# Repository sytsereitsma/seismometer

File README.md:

MC3479
NSCDJJN005NDUNV

# Filters
https://www.allaboutcircuits.com/video-tutorials/op-amps-low-pass-and-high-pass-active-filters/
http://sim.okawa-denshi.jp/en/OPstool.php
https://tools.analog.com/en/filterwizard/

https://electronics.stackexchange.com/questions/55233/how-do-you-simulate-voltage-noise-with-ltspice
https://electronics.stackexchange.com/questions/291721/how-to-implement-frequency-sweep-in-transient-mode-in-ltspice

## LTSpice

`.step param freq list 0.01 0.1 1 2 4 8 10 12` en dan BV voltage source (misc components) met `V=0.015*sin(2*pi*freq*time)`

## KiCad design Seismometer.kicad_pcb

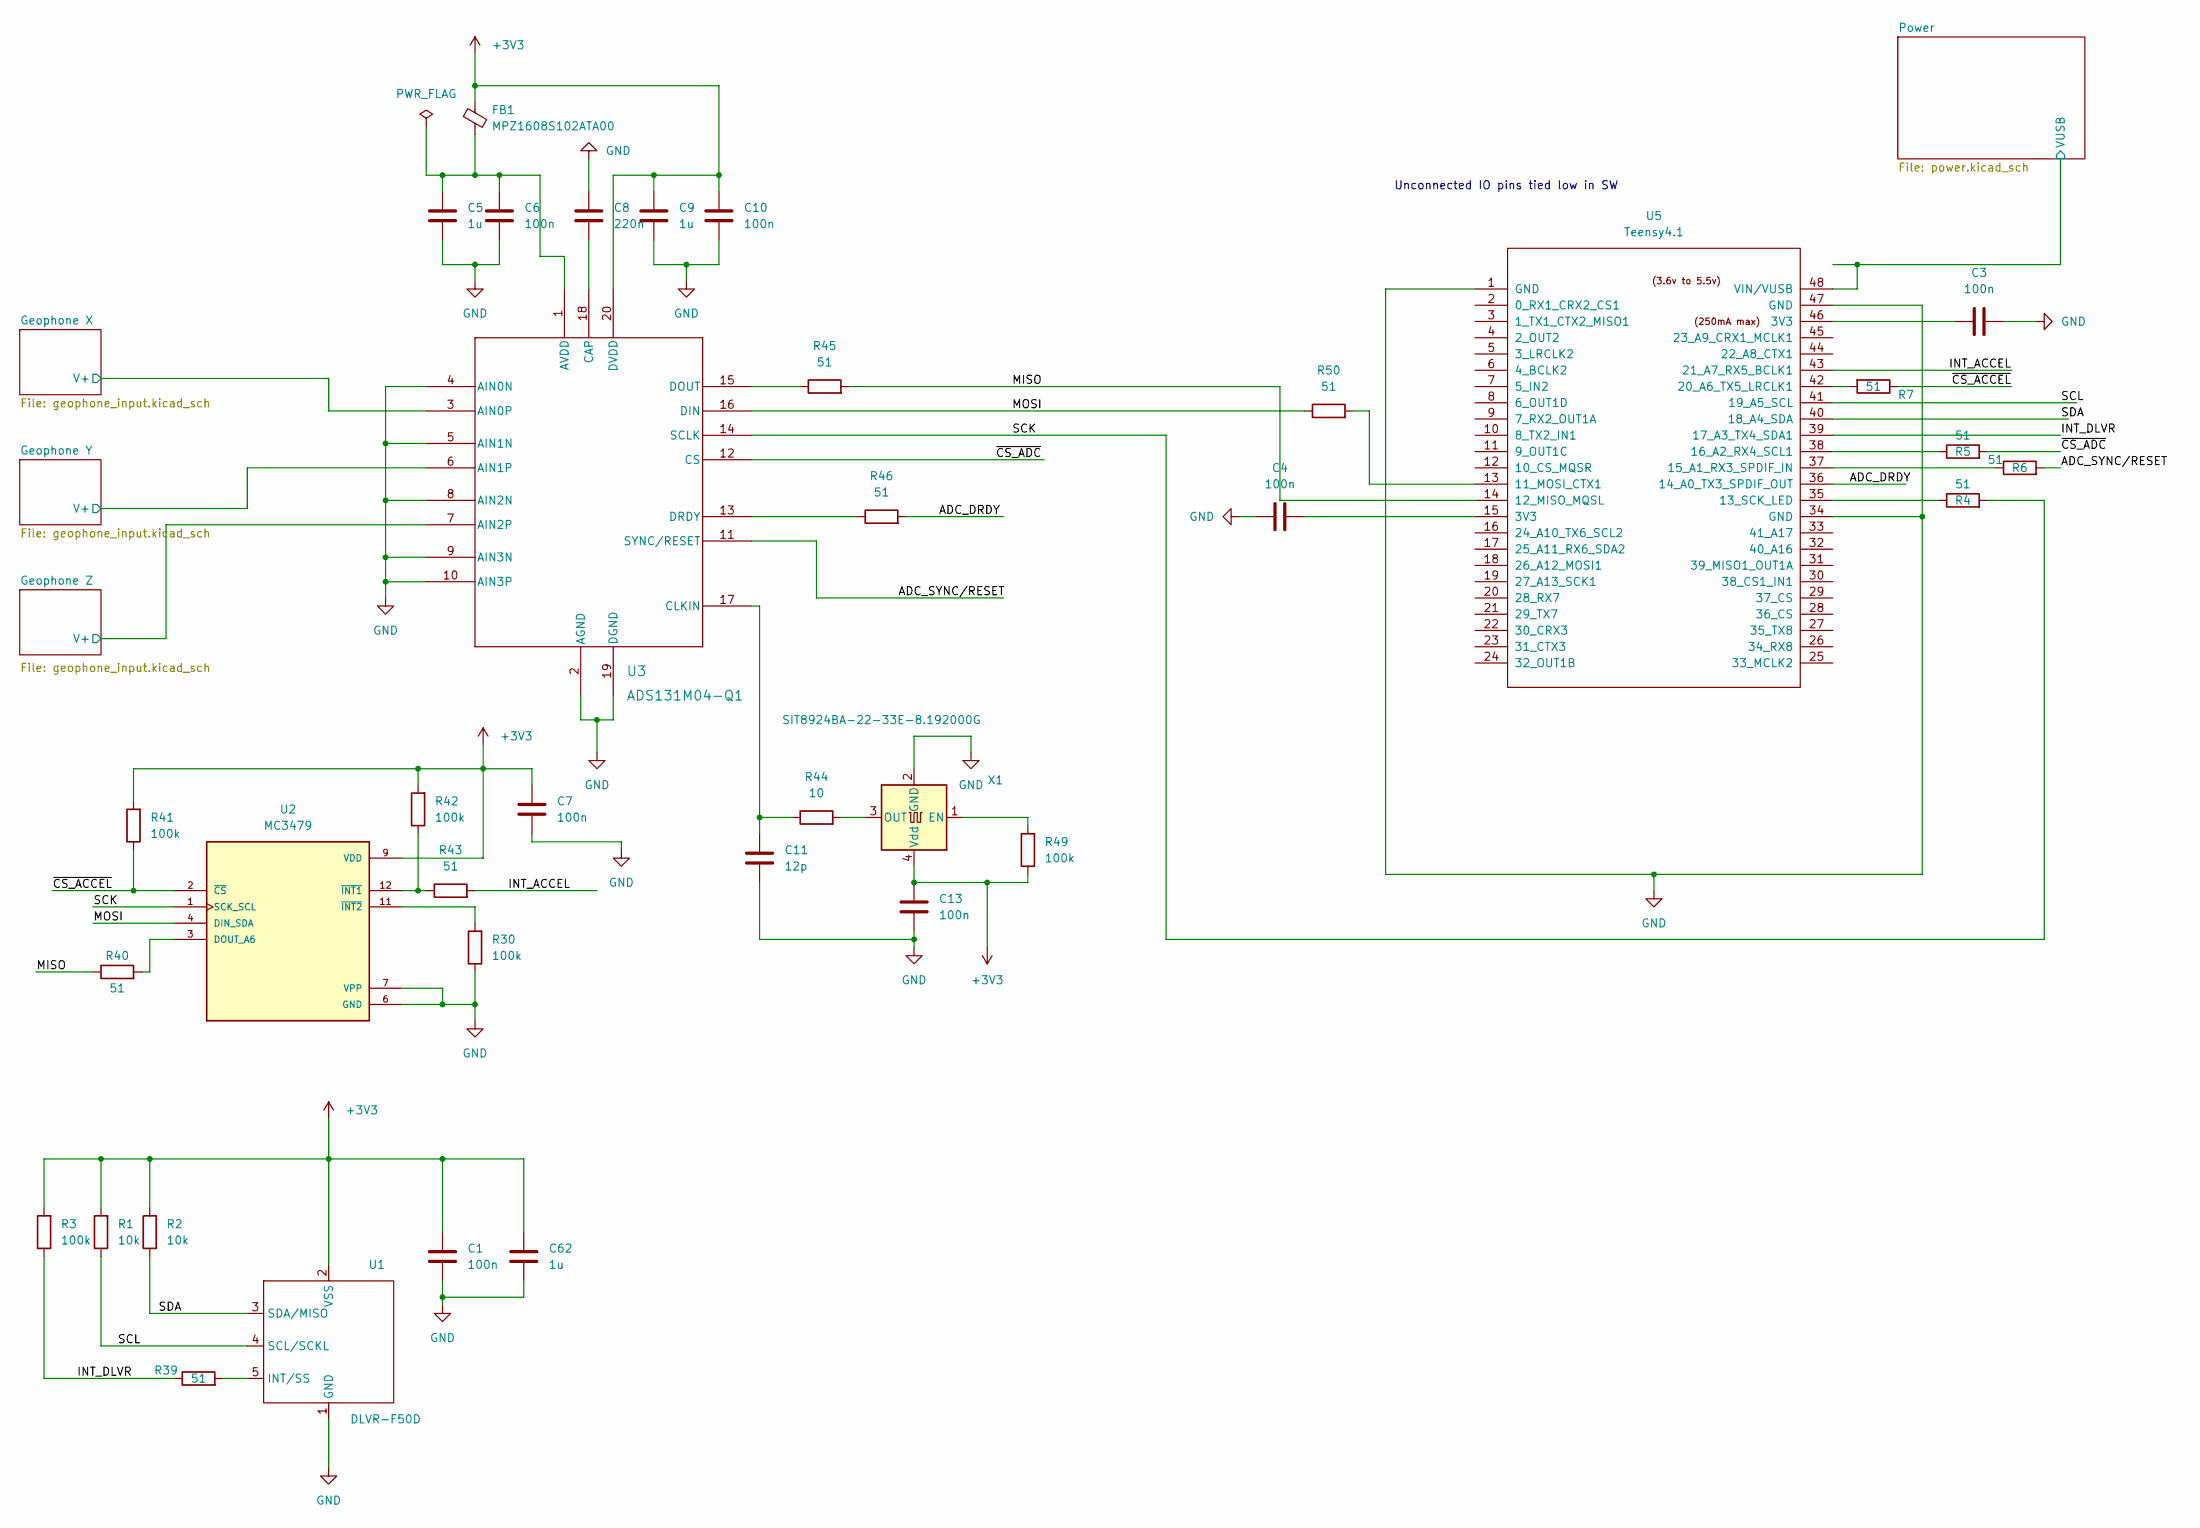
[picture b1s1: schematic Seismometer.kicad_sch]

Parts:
C1, C3, C4, C6, C7, C10, C13: 100n; C_0603_1608Metric_Pad1.08x0.95mm_HandSolder
C5, C9, C62: 1u; C_1206_3216Metric
C8: 220n; C_0603_1608Metric_Pad1.08x0.95mm_HandSolder
C11: 12p; C_0603_1608Metric_Pad1.08x0.95mm_HandSolder
FB1: MPZ1608S102ATA00; L_0805_2012Metric
R1, R2: 10k; R_0603_1608Metric
R3, R30, R41, R42, R49: 100k; R_0603_1608Metric
R4, R5, R6, R7, R39, R40, R43, R45, R46, R50: 51; R_0603_1608Metric
R44: 10; R_0603_1608Metric
U1: DLVR-F50D; DIP-8_W8.89mm_SMDSocket_LongPads
U2: MC3479; PQFN50P200X200X100-12N; PARTREV 1.1
U3: ADS131M04-Q1; TSSOP20_PW_TEX
U5: Teensy4.1; Teensy41_minimal
X1: SIT8924BA-22-33E-8.192000G; Oscillator_SMD_Abracon_ASE-4Pin_3.2x2.5mm

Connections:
+3V3: C1.1, C7.1, C9.1, C10.1, C13.1, C62.1, FB1.1, R1.2, R2.2, R3.2, R41.2, R42.2, R49.1, U1.2 (VSS), U2.9 (VDD), U3.20 (DVDD), X1.4 (Vdd); also elsewhere on the board
/ADC_DRDY: R46.2, U5.36 (14_A0_TX3_SPDIF_OUT)
/ADC_SYNC/RESET: R6.2, U3.11 (SYNC/RESET)
/Geophone X/V+: U3.3 (AIN0P); also elsewhere on the board
/Geophone Y/V+: U3.6 (AIN1P); also elsewhere on the board
/Geophone Z/V+: U3.7 (AIN2P); also elsewhere on the board
/INT_ACCEL: R43.2, U5.43 (21_A7_RX5_BCLK1)
/INT_DLVR: R3.1, R39.1, U5.39 (17_A3_TX4_SDA1)
/MISO: R40.1, R45.2, U5.14 (12_MISO_MQSL)
/MOSI: R50.1, U2.4 (DIN_SDA), U3.16 (DIN)
/Power/VUSB: U5.48 (VIN/VUSB); also elsewhere on the board
/SCK: R4.2, U2.1 (SCK_SCL), U3.14 (SCLK)
/SCL: R1.1, U1.4 (SCL/SCKL), U5.41 (19_A5_SCL)
/SDA: R2.1, U1.3 (SDA/MISO), U5.40 (18_A4_SDA)
/~CS_ACCEL: R7.1, R41.1, U2.2 (~CS)
/~CS_ADC: R5.2, U3.12 (CS)
GND: C1.2, C3.2, C4.1, C5.2, C6.2, C7.2, C8.1, C9.2, C10.2, C11.2, C13.2, C62.2, R30.1, U1.1 (GND), U2.6 (GND), U2.7 (VPP), U3.2 (AGND), U3.4 (AIN0N), U3.5 (AIN1N), U3.8 (AIN2N), U3.9 (AIN3N), U3.10 (AIN3P), U3.19 (DGND), U5.1 (GND), U5.34 (GND), U5.47 (GND), X1.2 (GND); also elsewhere on the board
unnamed: C3.1, U5.46 (3V3)
unnamed: C4.2, U5.15 (3V3)
unnamed: R39.2, U1.5 (INT/SS)
unnamed: R40.2, U2.3 (DOUT_A6)
unnamed: R42.1, R43.1, U2.12 (~INT1)
unnamed: R30.2, U2.11 (~INT2)
unnamed: C5.1, C6.1, FB1.2, U3.1 (AVDD)
unnamed: C8.2, U3.18 (CAP)
unnamed: C11.1, R44.1, U3.17 (CLKIN)
unnamed: R45.1, U3.15 (DOUT)
unnamed: R46.1, U3.13 (DRDY)
unnamed: R50.2, U5.13 (11_MOSI_CTX1)
unnamed: R4.1, U5.35 (13_SCK_LED)
unnamed: R6.1, U5.37 (15_A1_RX3_SPDIF_IN)
unnamed: R5.1, U5.38 (16_A2_RX4_SCL1)
unnamed: R7.2, U5.42 (20_A6_TX5_LRCLK1)
unnamed: R49.2, X1.1 (EN)
unnamed: R44.2, X1.3 (OUT)

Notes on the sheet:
Unconnected IO pins tied low in SW

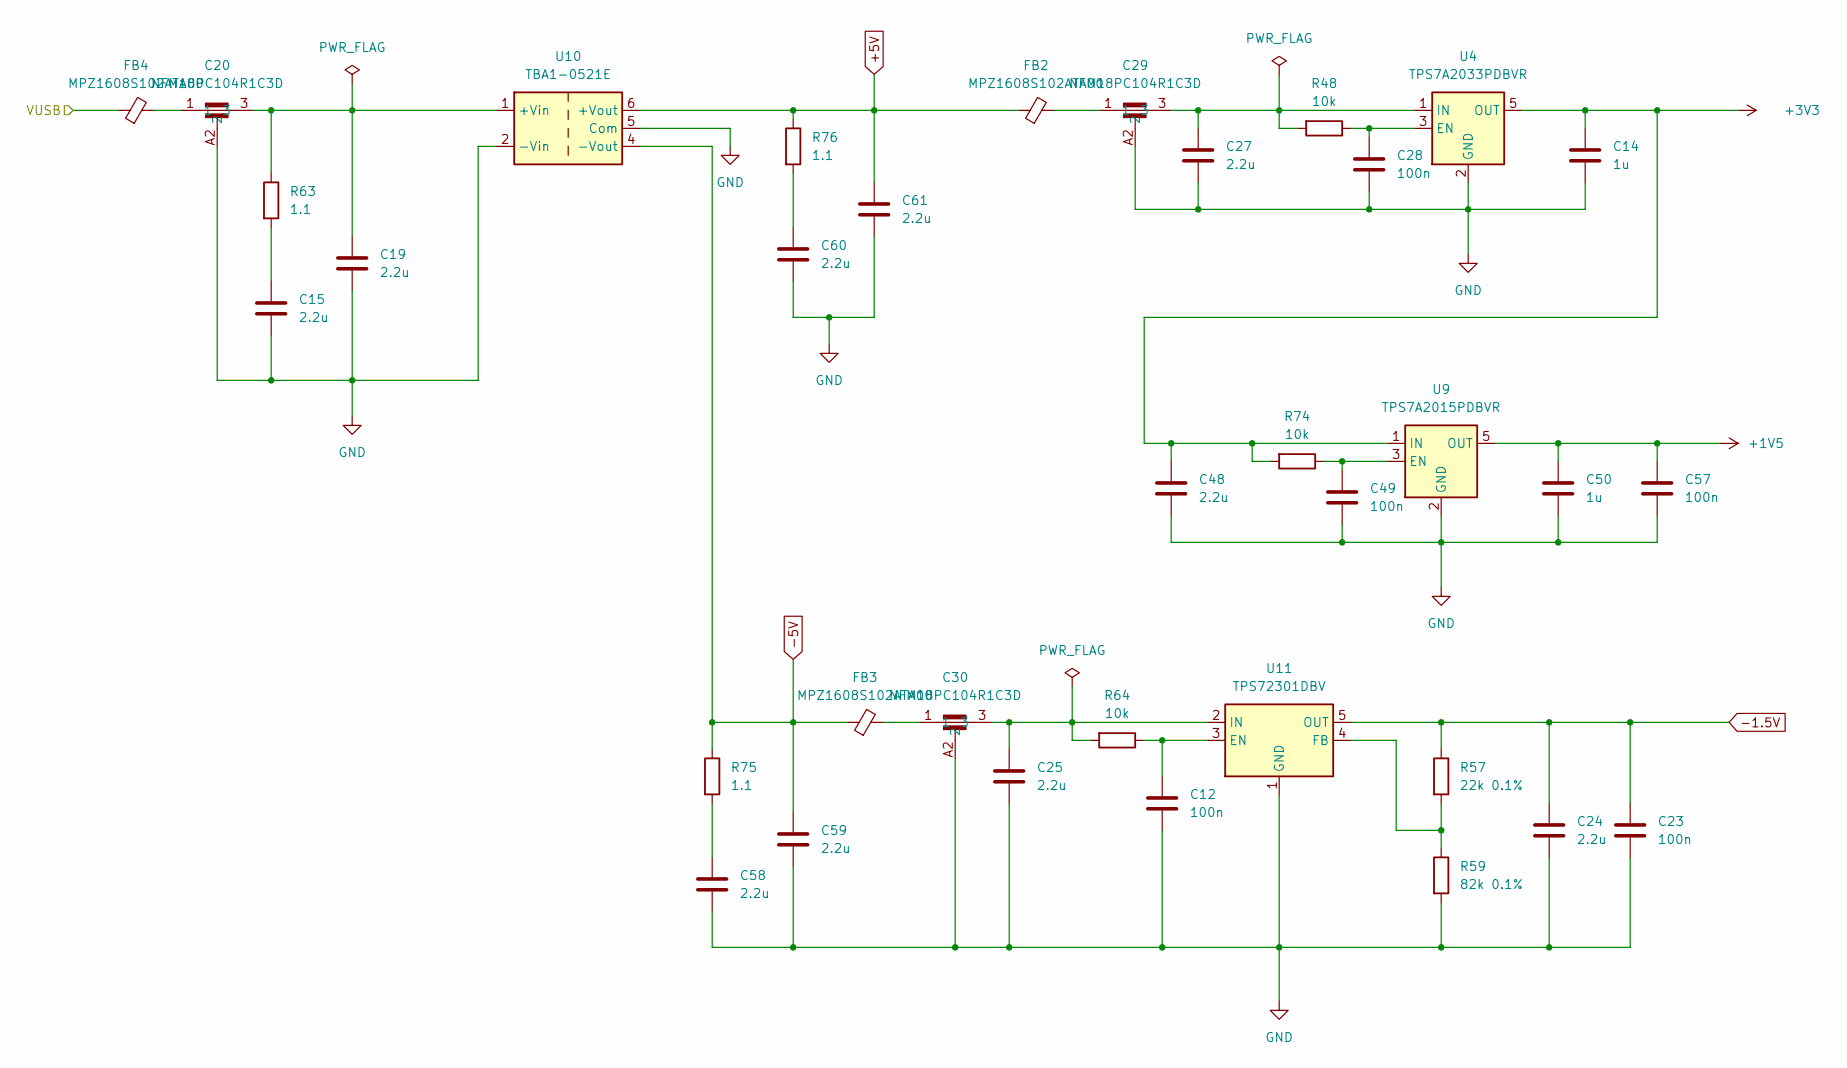
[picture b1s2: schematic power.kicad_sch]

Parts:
C12, C28, C49: 100n; C_0603_1608Metric_Pad1.08x0.95mm_HandSolder
C14, C50: 1u; C_1206_3216Metric
C15, C19, C24, C25, C27, C48, C58, C59, C60, C61: 2.2u; C_1206_3216Metric
C20, C29, C30: NFM18PC104R1C3D
C23, C57: 100n; C_0805_2012Metric
FB2, FB3, FB4: MPZ1608S102ATA00; L_0805_2012Metric
R48, R64, R74: 10k; R_0603_1608Metric
R57: 22k 0.1%; R_0603_1608Metric
R59: 82k 0.1%; R_0603_1608Metric
R63, R75, R76: 1.1; R_0603_1608Metric
U4: TPS7A2033PDBVR; SOT-23-5
U9: TPS7A2015PDBVR; SOT-23-5
U10: TBA1-0521E; Converter_DCDC_TRACO_TBA1-xxxxE_Dual_THT
U11: TPS72301DBV; SOT-23-5

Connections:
+1V5: C50.1, C57.1, U9.5 (OUT); also elsewhere on the board
+3V3: C14.1, C48.1, R74.2, U4.5 (OUT), U9.1 (IN); also elsewhere on the board
+5V: C61.1, FB2.1, R76.1, U10.6 (+Vout)
-1.5V: C23.1, C24.1, R57.1, U11.5 (OUT); also elsewhere on the board
-5V: C59.1, FB3.1, R75.1, U10.4 (-Vout)
/Power/VUSB: FB4.1; also elsewhere on the board
GND: C12.2, C14.2, C15.2, C19.2, C20.A2 (2), C20.B2 (4), C23.2, C24.2, C25.2, C27.2, C28.2, C29.A2 (2), C29.B2 (4), C30.A2 (2), C30.B2 (4), C48.2, C49.2, C50.2, C57.2, C58.2, C59.2, C60.2, C61.2, R59.2, U4.2 (GND), U9.2 (GND), U10.2 (-Vin), U10.5 (Com), U11.1 (GND); also elsewhere on the board
unnamed: C15.1, R63.2
unnamed: C20.1, FB4.2
unnamed: C29.1, FB2.2
unnamed: C30.1, FB3.2
unnamed: C58.1, R75.2
unnamed: C60.1, R76.2
unnamed: C28.1, R48.1, U4.3 (EN)
unnamed: C27.1, C29.3, R48.2, U4.1 (IN)
unnamed: C49.1, R74.1, U9.3 (EN)
unnamed: C19.1, C20.3, R63.1, U10.1 (+Vin)
unnamed: C12.1, R64.1, U11.3 (EN)
unnamed: R57.2, R59.1, U11.4 (FB)
unnamed: C25.1, C30.3, R64.2, U11.2 (IN)

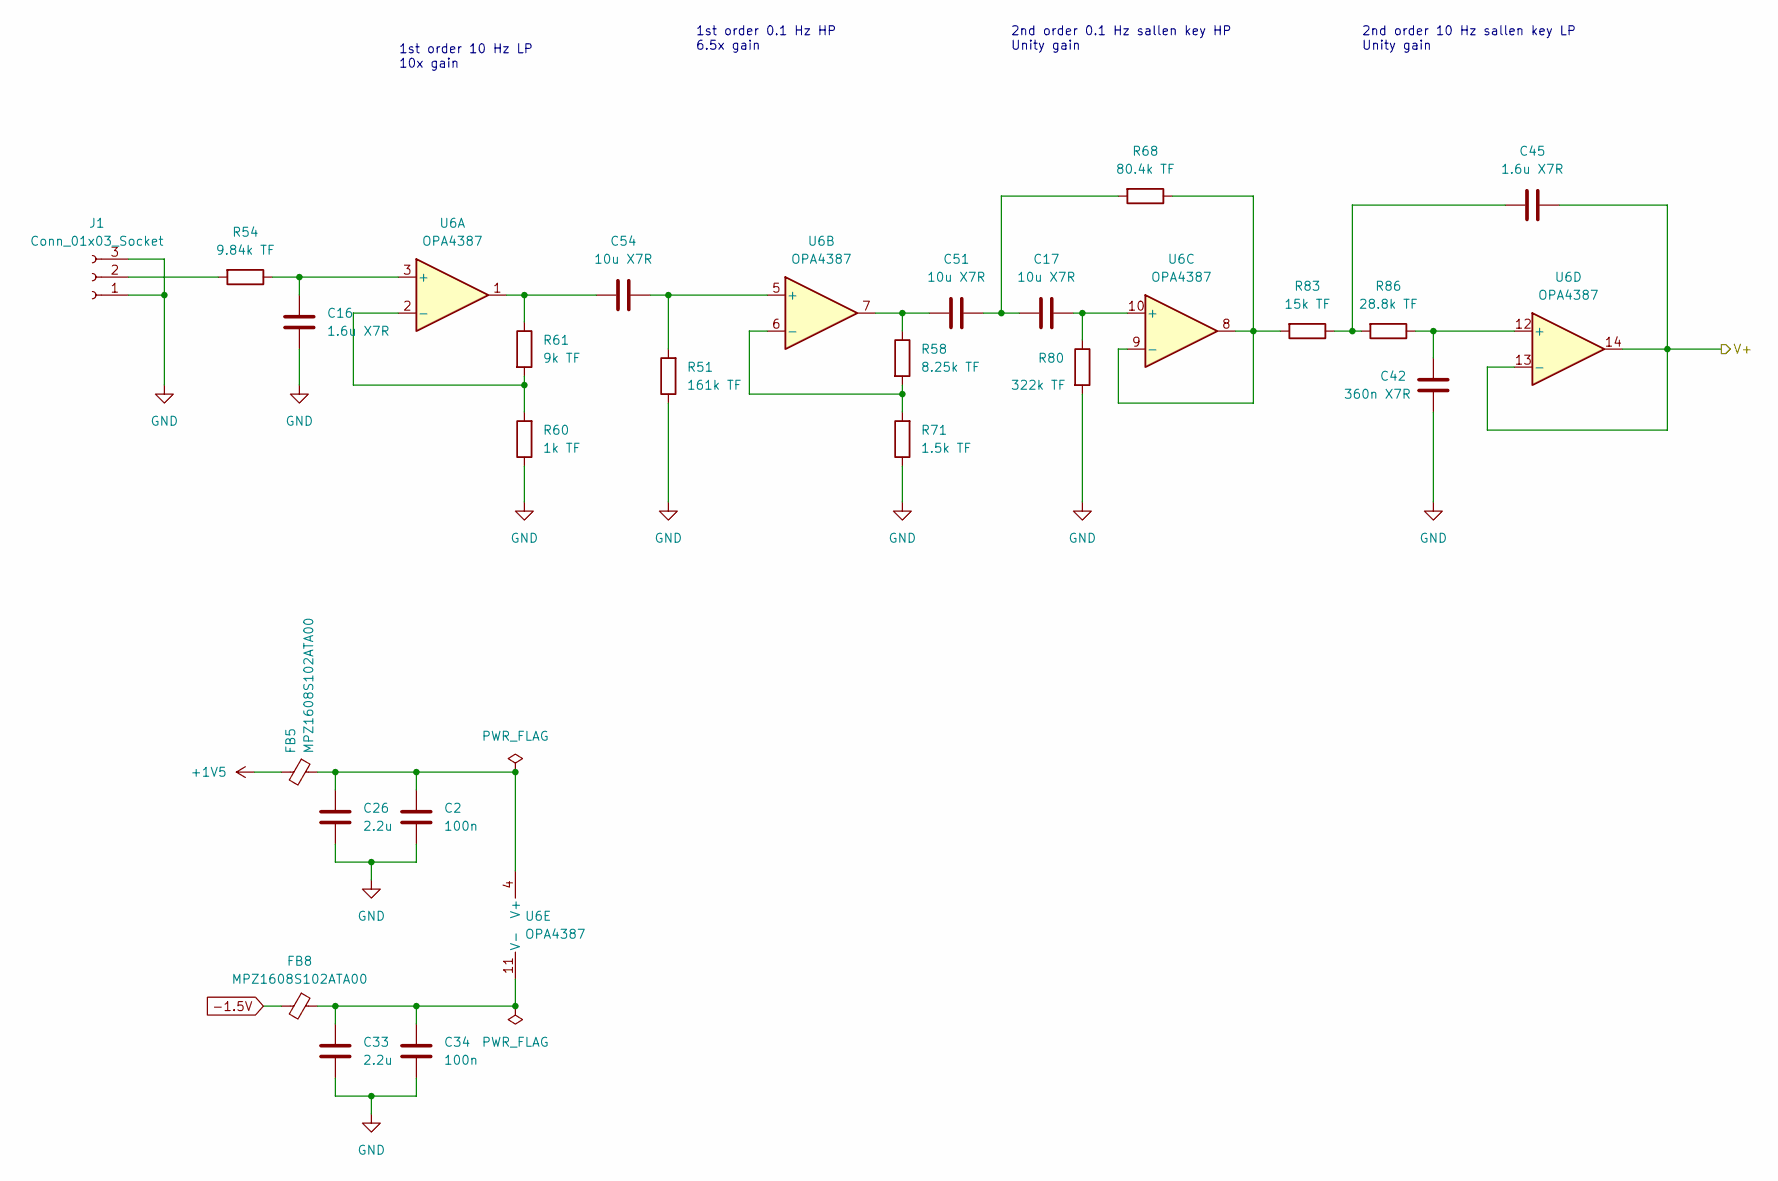
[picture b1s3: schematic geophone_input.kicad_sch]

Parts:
C2, C34: 100n; C_0603_1608Metric_Pad1.08x0.95mm_HandSolder
C16, C45: 1.6u X7R; C_1206_3216Metric
C17, C51, C54: 10u X7R; C_1206_3216Metric
C26, C33: 2.2u; C_1206_3216Metric
C42: 360n X7R; C_0805_2012Metric_Pad1.18x1.45mm_HandSolder
FB5, FB8: MPZ1608S102ATA00; L_0805_2012Metric
J1: Conn_01x03_Socket; PinHeader_1x03_P2.54mm_Horizontal
R51: 161k TF; R_0603_1608Metric_Pad0.98x0.95mm_HandSolder
R54: 9.84k TF; R_0603_1608Metric_Pad0.98x0.95mm_HandSolder
R58: 8.25k TF; R_0603_1608Metric_Pad0.98x0.95mm_HandSolder
R60: 1k TF; R_0603_1608Metric_Pad0.98x0.95mm_HandSolder
R61: 9k TF; R_0603_1608Metric_Pad0.98x0.95mm_HandSolder
R68: 80.4k TF; R_0603_1608Metric_Pad0.98x0.95mm_HandSolder
R71: 1.5k TF; R_0603_1608Metric_Pad0.98x0.95mm_HandSolder
R80: 322k TF; R_0603_1608Metric_Pad0.98x0.95mm_HandSolder
R83: 15k TF; R_0603_1608Metric_Pad0.98x0.95mm_HandSolder
R86: 28.8k TF; R_0603_1608Metric_Pad0.98x0.95mm_HandSolder
U6: OPA4387; TSSOP-14_4.4x5mm_P0.65mm

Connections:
+1V5: FB5.2; also elsewhere on the board
-1.5V: FB8.2; also elsewhere on the board
/Geophone X/V+: C45.2, U6.13 (-), U6.14; also elsewhere on the board
GND: C2.1, C16.2, C26.1, C33.1, C34.1, C42.2, J1.1, J1.3, R51.1, R60.1, R71.1, R80.2; also elsewhere on the board
unnamed: C17.1, C51.1, R68.2
unnamed: C45.1, R83.1, R86.2
unnamed: C51.2, R58.1, U6.7
unnamed: C54.1, R61.1, U6.1
unnamed: J1.2, R54.2
unnamed: C16.1, R54.1, U6.3 (+)
unnamed: R60.2, R61.2, U6.2 (-)
unnamed: C54.2, R51.2, U6.5 (+)
unnamed: R58.2, R71.2, U6.6 (-)
unnamed: C17.2, R80.1, U6.10 (+)
unnamed: R68.1, R83.2, U6.8, U6.9 (-)
unnamed: C42.1, R86.1, U6.12 (+)
unnamed: C2.2, C26.2, FB5.1, U6.4 (V+)
unnamed: C33.2, C34.2, FB8.1, U6.11 (V-)

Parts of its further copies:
C18, C39, C46, C47: 1.6u X7R; C_1206_3216Metric
C21, C22, C36, C38: 100n; C_0603_1608Metric_Pad1.08x0.95mm_HandSolder
C31, C32, C35, C37: 2.2u; C_1206_3216Metric
C40, C41, C52, C53, C55, C56: 10u X7R; C_1206_3216Metric
C43, C44: 360n X7R; C_0805_2012Metric_Pad1.18x1.45mm_HandSolder
FB6, FB7, FB9, FB10: MPZ1608S102ATA00; L_0805_2012Metric
J2, J3: Conn_01x03_Socket; PinHeader_1x03_P2.54mm_Horizontal
R52, R53: 161k TF; R_0603_1608Metric_Pad0.98x0.95mm_HandSolder
R55, R56: 9.84k TF; R_0603_1608Metric_Pad0.98x0.95mm_HandSolder
R62, R66: 1k TF; R_0603_1608Metric_Pad0.98x0.95mm_HandSolder
R65, R67: 9k TF; R_0603_1608Metric_Pad0.98x0.95mm_HandSolder
R69, R70: 80.4k TF; R_0603_1608Metric_Pad0.98x0.95mm_HandSolder
R72, R73: 1.5k TF; R_0603_1608Metric_Pad0.98x0.95mm_HandSolder
R77, R79: 8.25k TF; R_0603_1608Metric_Pad0.98x0.95mm_HandSolder
R81, R82: 322k TF; R_0603_1608Metric_Pad0.98x0.95mm_HandSolder
R84, R85: 15k TF; R_0603_1608Metric_Pad0.98x0.95mm_HandSolder
R87, R88: 28.8k TF; R_0603_1608Metric_Pad0.98x0.95mm_HandSolder
U7, U8: OPA4387; TSSOP-14_4.4x5mm_P0.65mm

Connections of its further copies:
+1V5: FB6.2, FB7.2; also elsewhere on the board
-1.5V: FB9.2, FB10.2; also elsewhere on the board
/Geophone Y/V+: C46.2, U7.13 (-), U7.14; also elsewhere on the board
/Geophone Z/V+: C47.2, U8.13 (-), U8.14; also elsewhere on the board
GND: C18.2, C21.1, C22.1, C31.1, C32.1, C35.1, C36.1, C37.1, C38.1, C39.2, C43.2, C44.2, J2.1, J2.3, J3.1, J3.3, R52.1, R53.1, R62.1, R66.1, R72.1, R73.1, R81.2, R82.2; also elsewhere on the board
unnamed: C40.1, C52.1, R69.2
unnamed: C41.1, C53.1, R70.2
unnamed: C46.1, R84.1, R87.2
unnamed: C47.1, R85.1, R88.2
unnamed: C52.2, R77.1, U7.7
unnamed: C53.2, R79.1, U8.7
unnamed: C55.1, R65.1, U7.1
unnamed: C56.1, R67.1, U8.1
unnamed: J2.2, R55.2
unnamed: J3.2, R56.2
unnamed: C18.1, R55.1, U7.3 (+)
unnamed: R62.2, R65.2, U7.2 (-)
unnamed: C55.2, R52.2, U7.5 (+)
unnamed: R72.2, R77.2, U7.6 (-)
unnamed: C40.2, R81.1, U7.10 (+)
unnamed: R69.1, R84.2, U7.8, U7.9 (-)
unnamed: C43.1, R87.1, U7.12 (+)
unnamed: C21.2, C31.2, FB6.1, U7.4 (V+)
unnamed: C35.2, C36.2, FB9.1, U7.11 (V-)
unnamed: C39.1, R56.1, U8.3 (+)
unnamed: R66.2, R67.2, U8.2 (-)
unnamed: C56.2, R53.2, U8.5 (+)
unnamed: R73.2, R79.2, U8.6 (-)
unnamed: C41.2, R82.1, U8.10 (+)
unnamed: R70.1, R85.2, U8.8, U8.9 (-)
unnamed: C44.1, R88.1, U8.12 (+)
unnamed: C22.2, C32.2, FB7.1, U8.4 (V+)
unnamed: C37.2, C38.2, FB10.1, U8.11 (V-)

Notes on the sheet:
2nd order 0.1 Hz sallen key HP Unity gain
1st order 10 Hz LP 10x gain
1st order 0.1 Hz HP 6.5x gain
2nd order 10 Hz sallen key LP Unity gain

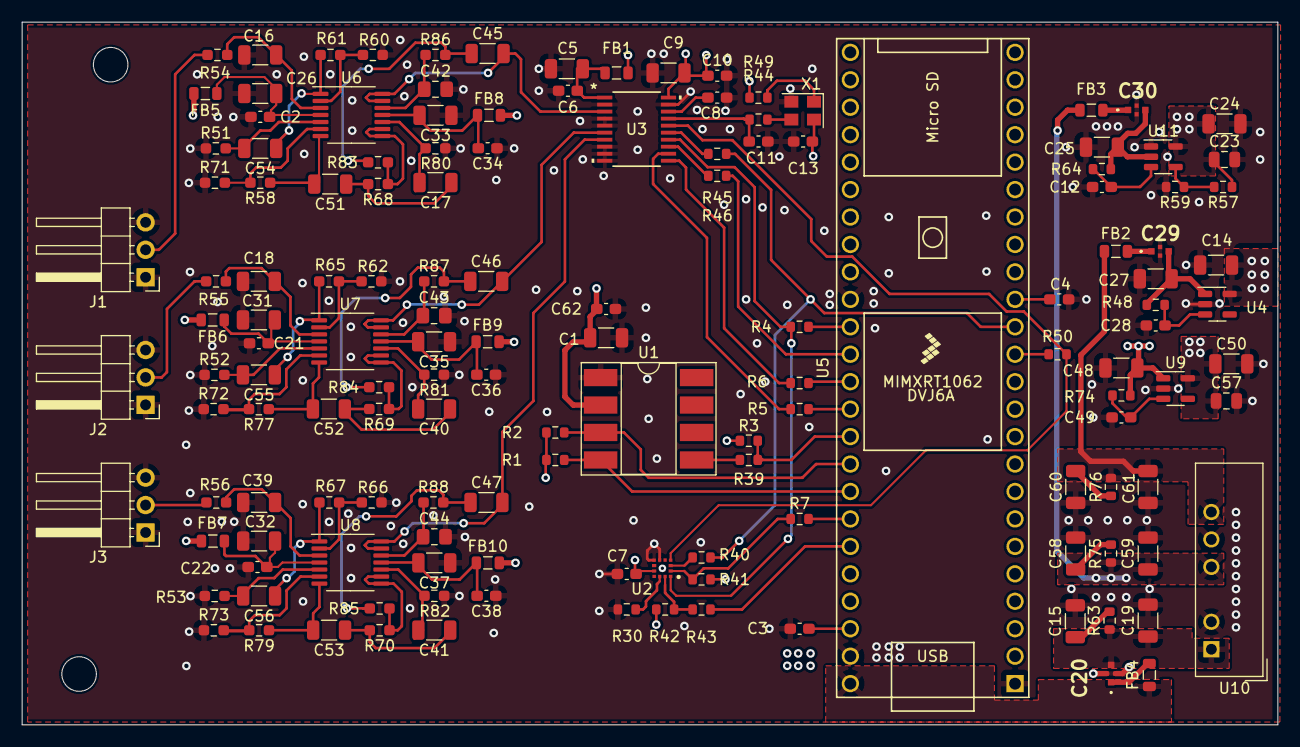
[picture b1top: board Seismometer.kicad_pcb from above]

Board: 4 copper layers, 116.2 x 65.0 mm, 143 parts (0 on the bottom side), 94 nets.

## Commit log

2024-01-11 Finishing schematic
2024-01-11 Layout
2024-01-12 Initial layout complete
2024-01-12 Ready
2024-04-13 Active input filter
2024-04-19 wip Layout
2024-04-24 Layout done. Tweaking...
2024-09-26 wip No idea? Better filters?
2024-09-27 Recording engine working
2024-09-27 Gain of 64x
2024-09-29 Working detection
2024-09-29 New detection algorithm
2024-09-29 firmware
2024-10-10 Cleanup
2024-10-12 More configuration options for the event processing Code cleanup
2024-10-13 wip Trying out different trigger detectors
2024-10-13 Simpler trigger detector
2024-10-13 Added boilerplate trait for running record handler threads
2024-10-13 Optionally log raw data
2024-10-14 Better filtering, more unit tests, debugging
2024-10-14 Re-enabled FIR filter
2024-10-14 Some debug scripting
2024-10-19 Dealing with huge logfiles, index the logfile and read chuncks of it
2024-10-19 Removed unneeded nested lifetime
